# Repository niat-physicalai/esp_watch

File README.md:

# ESP Watch

A custom ESP32-C3-based wearable device that combines a small OLED display, motion sensing, heart-rate sensing,
Wi-Fi/BLE connectivity, and a LiPo battery into a compact wrist-worn platform.

The project covers the complete product-development workflow — from breadboard prototyping and firmware development
to schematic capture, custom PCB design, fabrication, and enclosure CAD.

## Features

* **Seeed XIAO ESP32-C3**
* **0.96" 128×64 SSD1306 OLED**
* **MPU-6050** 6-axis IMU
* **MAX30102** heart-rate / SpO₂ sensor
* 2 user buttons
* LiPo battery operation
* Wi-Fi / Bluetooth Low Energy
* Custom 2-layer carrier PCB
* 3D-printed enclosure

---

## Hardware

| Component         | Details                    |
| ----------------- | -------------------------- |
| MCU               | XIAO ESP32-C3              |
| Display           | SSD1306 OLED, 128×64       |
| IMU               | MPU-6050                   |
| Heart-rate sensor | MAX30102                   |
| Communication     | Wi-Fi + BLE                |
| Power             | LiPo                       |
| PCB               | Custom 38 × 38 mm, 2-layer |

## System Architecture
                         LiPo Battery
                              │
                       Optional Switch
                              │
                       XIAO BAT+ / BAT-
                              │
                    ┌─────────┴─────────┐
                    │                   │
                 XIAO ESP32-C3       Charger
                    │
                  3.3 V
                    │
          ┌─────────┼──────────┐
          │         │          │
       SSD1306   MPU-6050   MAX30102
       OLED       IMU       HR / SpO₂
       0x3C       0x68         0x57
          │         │          │
          └─────────┴──────────┘
                 I²C Bus
             SDA = GPIO6
             SCL = GPIO7

       GPIO10 ── Next Button
       GPIO3 ── Previous Button

### Pinout

| XIAO Pin     | Function        |
| ------------ | --------------- |
| D4 / GPIO6   | I²C SDA         |
| D5 / GPIO7   | I²C SCL         |
| D10 / GPIO10 | Next button     |
| D1 / GPIO3   | Previous button |

The OLED, MPU-6050 and MAX30102 share the I²C bus. No interrupt pins are used for the MPU-6050 or MAX30102.

### Battery

The reference design currently treats the battery as a placeholder. The documented placeholder is:

Capacity: 400 mAh
Approximate dimensions: 20 × 5 × 13 mm

---

## Breadboard Prototype

The watch electronics were first assembled and tested on a breadboard before moving to the custom PCB.

**Figure 1 — Breadboard prototype**

*Initial ESP32-C3 smartwatch prototype with the display and sensor modules connected for firmware and hardware testing.*

Additional prototype photos are available in [`asset/breadboard/`](asset/breadboard/).

---

## Circuit Schematic

The final circuit was designed around the XIAO ESP32-C3 with the display and sensors connected through the I²C bus.

**Figure 2 — Circuit schematic**

*Complete schematic of the ESP Watch carrier board.*

---

## PCB Design

The prototype was converted into a custom 2-layer carrier PCB measuring approximately **38 × 38 mm**.

The custom carrier PCB is:
* 38 × 38 mm
* 2-layer
* Module-based design
* Custom KiCad schematic symbols
* Custom MAX30102 footprint
* Ground pours on both layers
* Hand-assembly oriented

**Figure 3 — PCB top view**

*Fully rendered top view showing the component placement and routing of the ESP Watch PCB.*

**Figure 4 — PCB front copper**

*Front copper layer showing signal and power routing.*

The repository also contains additional PCB views and renders in [`asset/pcb/`](asset/pcb/).

---

## Firmware

Firmware is written in Arduino C++ and can be developed using:

* **Arduino IDE** — `firmware/Arduino-IDE/`
* **PlatformIO** — `firmware/PlatformIO/`

The firmware interfaces with the display and sensors over I²C and handles the watch UI, buttons, motion and heart-rate functionality.

---

## Getting Started
### 1. Clone the repository
```bash
git clone https://github.com/niat-physicalai/esp_watch.git
cd esp_watch
```

### 2. Firmware

Choose one of the supported development environments:

firmware/
├── Arduino-IDE/
└── PlatformIO/

### Arduino IDE

Open:

`firmware/Arduino-IDE/esp_watch/esp_watch.ino`

Select the appropriate ESP32-C3 board configuration and upload the firmware.

### PlatformIO

Open:

`firmware/PlatformIO/esp_watch/`

using VS Code with the PlatformIO extension.

Then build and upload the project.

*Note** Exact board-manager/library versions and firmware configuration requirements should be verified against the current project files before treating them as fixed requirements.

---

## Repository Structure

```text
esp_watch/
├── asset/
│   ├── breadboard/      # Prototype photos
│   └── pcb/             # PCB renders and schematic
│
├── firmware/
│   ├── Arduino-IDE/     # Arduino IDE firmware
│   └── PlatformIO/      # PlatformIO project
│
├── README.md
└── dir.txt
```

---

## Status

* [x] Breadboard prototype
* [x] Firmware
* [x] PCB design
* [ ] PCB fabrication / assembly
* [ ] Enclosure development

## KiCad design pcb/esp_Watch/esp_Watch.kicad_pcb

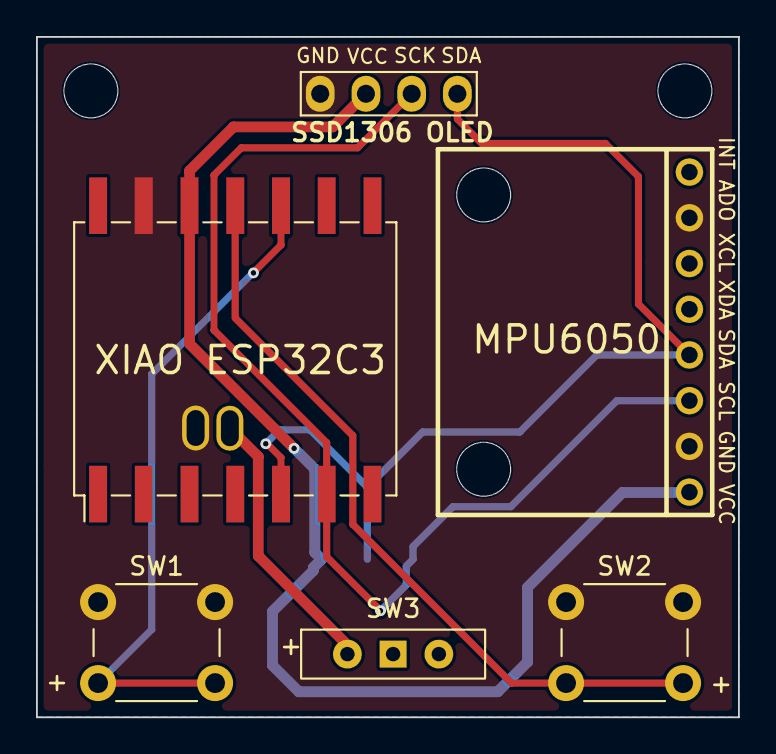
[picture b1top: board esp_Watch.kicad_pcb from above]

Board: 2 copper layers, 39.0 x 37.8 mm, 7 parts (1 on the bottom side), 7 nets.

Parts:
MAX30102: MAX30102 module
MPU-6050_module1: GY-521 MPU6050 MODULE FOOTPRINT
SSD1306 OLED: 128x64OLED
SW1, SW2: SW_Push; SW_PUSH_6mm
SW3: SW_Nidec_CAS-120A1; SW_Slide-03_Wuerth-WS-SLTV_10x2.5x6.4_P2.54mm
XIAO ESP32C3: XIAO ESP32C3; xiao_esp32c3

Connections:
+3V3: MAX30102.8 (VCC), MPU-6050_module1.8 (VCC), SSD1306 OLED.2 (VCC), XIAO ESP32C3.12 (VCC_3V3)
GND: MAX30102.5 (GND), MPU-6050_module1.2 (AD0), MPU-6050_module1.7 (GND), SSD1306 OLED.1 (GND), SW1.1, SW2.1, XIAO ESP32C3.13 (GND), XIAO ESP32C3.B- (Batt-)
unnamed: SW3.2 (B), XIAO ESP32C3.B+ (Batt+)
unnamed: SW1.2, XIAO ESP32C3.10 (D9)
unnamed: SW2.2, XIAO ESP32C3.11 (D10)
SCL: MAX30102.6 (SCL), MPU-6050_module1.6 (SCL), SSD1306 OLED.3 (SCK), XIAO ESP32C3.6 (D5)
SDA: MAX30102.7 (SDA), MPU-6050_module1.5 (SDA), SSD1306 OLED.4 (SDA), XIAO ESP32C3.5 (D4)
